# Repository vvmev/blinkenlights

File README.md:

# blinkenlights
Show random signal aspects using ESP8266 modules

## Hardware

We use Wemos D1 mini ESP8266 modules (or clones), with a number of [SI2302DS](https://www.vishay.com/docs/70628/70628.pdf) (PDF) N-channel MOSFETs as low-side switches.

We use XLR five-position connectors: female in the enclosure for the ESP8266, male on the consumers. The pin assignments are:

| XLR Pin | Cable  | Signal | Arduino |
| ------- | ------ | ------ | ------- |
| 1       | blue   | Out 1  | Pin D7  |
| 2       | yellow | Out 2  | Pin D6  |
| 3       | grey   | Out 3  | Pin D2  |
| 4       | black  | Out 4  | Pin D1  |
| 5       | brown  | +12V=  | -       |

## PCB

[d1mini-sw](d1mini-sw) contains Eagle files and matching Gerbers for a board compatible with the Wemos D1 Mini. For all seven GPIOs that can be used freely, a BSS138 (or compatible) MOSFET is connected as a low-side switch; the switched outputs are brought out on nine pads with 100mil spacing.  Input voltage for the ESP as well as a Vdd net is brought our on six pads with 100mil spacing.

## Sample Code

The Arduino Sketch [cycle-four-outputs](cycle-four-outputs) is a simple test programs that cycles on each of the four outputs in sequence, then turns them off, then starts over.

It also shows how to use [WiFi Manager](https://github.com/tzapu/WiFiManager) and [Arduino OTA](http://esp8266.github.io/Arduino/versions/2.0.0/doc/ota_updates/ota_updates.html).

### envmonitor

[envmonitor](envmonitor) shows how to read a DHT22 connected to pin D0 and post the data to MQTT. MQTT broker paramters have to be defined in [envmonitor/secrets.h](envmonitor/secrets.h), which is not checked in. See [envmonitor/secrets.h.example](envmonitor/secrets.h.example) for a sample file.

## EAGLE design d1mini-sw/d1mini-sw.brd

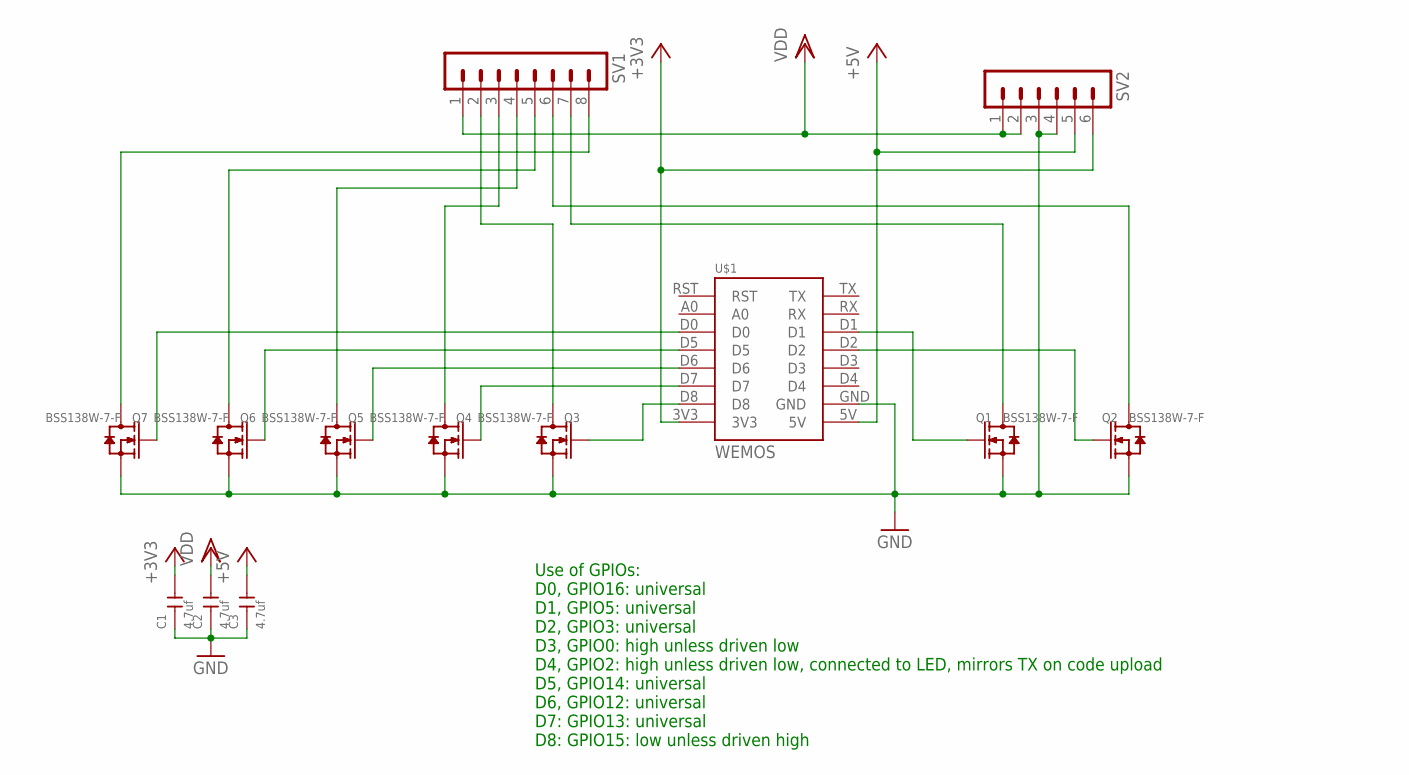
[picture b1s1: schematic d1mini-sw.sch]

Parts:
C1, C2, C3: 4.7uf; C0805
Q1, Q2, Q3, Q4, Q5, Q6, Q7: BSS138W-7-F; SOT-23
SV1: MA08-1
SV2: MA06-1
U$1: WEMOS

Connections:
+3V3: C1.2, SV2.6, U$1.3V3
+5V: C3.2, SV2.5, U$1.5V
D0: Q7.1 (G), U$1.D0
D1: Q1.1 (G), U$1.D1
D2: Q2.1 (G), U$1.D2
D5: Q6.1 (G), U$1.D5
D6: Q5.1 (G), U$1.D6
D7: Q4.1 (G), U$1.D7
D8: Q3.1 (G), U$1.D8
GND: C1.1, C2.1, C3.1, Q1.2 (S), Q2.2 (S), Q3.2 (S), Q4.2 (S), Q5.2 (S), Q6.2 (S), Q7.2 (S), SV2.3, SV2.4, U$1.GND
P0: Q7.3 (D), SV1.8
P1: Q1.3 (D), SV1.7
P2: Q2.3 (D), SV1.6
P5: Q6.3 (D), SV1.5
P6: Q5.3 (D), SV1.4
P7: Q4.3 (D), SV1.3
P8: Q3.3 (D), SV1.2
VDD: C2.2, SV1.1, SV2.1, SV2.2

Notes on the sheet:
Use of GPIOs: D0, GPIO16: universal D1, GPIO5: universal D2, GPIO3: universal D3, GPIO0: high unless driven low D4, GPIO2: high unless driven low, connected to LED, mirrors TX on code upload D5, GPIO14: universal D6, GPIO12: universal D7: GPIO13: universal D8: GPIO15: low unless driven high

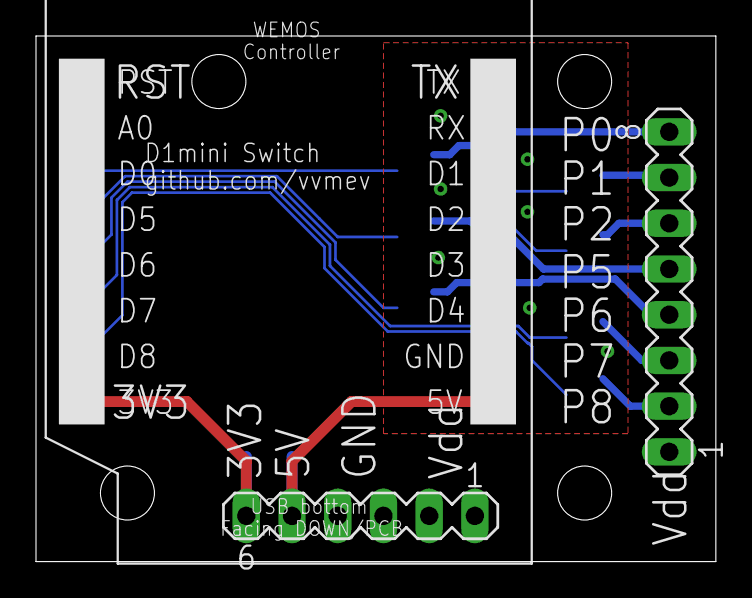
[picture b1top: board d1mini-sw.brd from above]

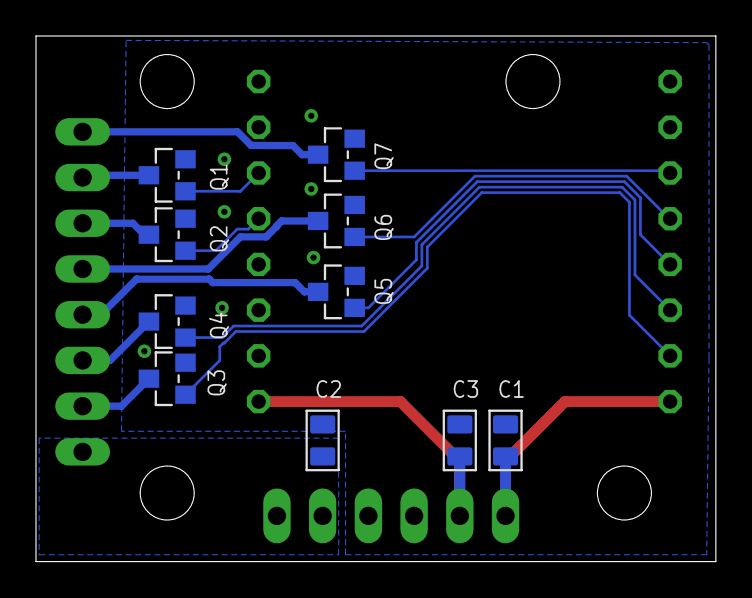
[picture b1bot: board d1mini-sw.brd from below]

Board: 2 copper layers, 37.8 x 29.2 mm, 13 parts (10 on the bottom side), 18 nets.

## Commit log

2017-11-12 Sketch to test the standard four-output setup.
    This will switch on output 1 to 4 in sequence, then have all off.
2017-11-12 add sv-signal
2017-11-12 Add cable specification
2017-11-12 Concrete code for one of the signals
2017-11-12 Give node a proper name
2017-11-12 Set name based on local part of MAC address
2017-11-14 host name correction
    host name correction
2018-01-06 Use ticker for stepping aspects
    Also reduce frequency to once every 10 seconds.
2018-01-10 add dht22-sketch, not working
2018-01-14 Add web control, birghtness
    Add a HTTP function to switch the automatic aspect cycling on or
    off, set the brightness and the current aspect. The home page
    shows appropriate buttons that reflect the status at the time the
    page was loaded.
    Also add PWM output so we can turn down the brightness at night.
2018-01-14 Correct comment
2018-02-14 Heartbeat and aspect stepper as ticker
2018-02-14 Post DHT22 data to MQTT
    DHT22 is connected to pin D0.
2018-02-16 Sketch to run the Hamburg S-Bahn Sv-Signal.
2018-03-05 Add board for switching outputs
2018-04-08 Set hostname to our custom name instead of the default ESPnnnn
